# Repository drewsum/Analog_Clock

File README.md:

# Analog_Clock
An Analog Meter clock
Controlled by PIC32MZ EF

U1001 firmware is programmed onto U1001 with a PIC KIT 4 through header J801 (this is PIC32MZ EF firmware).

U1302 flash image is programmed onto U1302 through USB connector J1301 using FTProg (this is FTDI USB/UART bridge flash contents).

Analog panel meters are installed at MES1801, MES1901 and MES2001. Analog panel meters selected for this project were bought on ebay at: https://www.ebay.com/itm/DC-0-15V-Analog-Voltmeter-Analogue-Voltage-panel-meter-SO45-directly-Connect/183077594391?ssPageName=STRK%3AMEBIDX%3AIT&_trksid=p2057872.m2749.l2649

Custom meter face plates are printed from a PDF in the /misc folder, to scale. They are inserted into the panel meters to allow the clock to display the time.

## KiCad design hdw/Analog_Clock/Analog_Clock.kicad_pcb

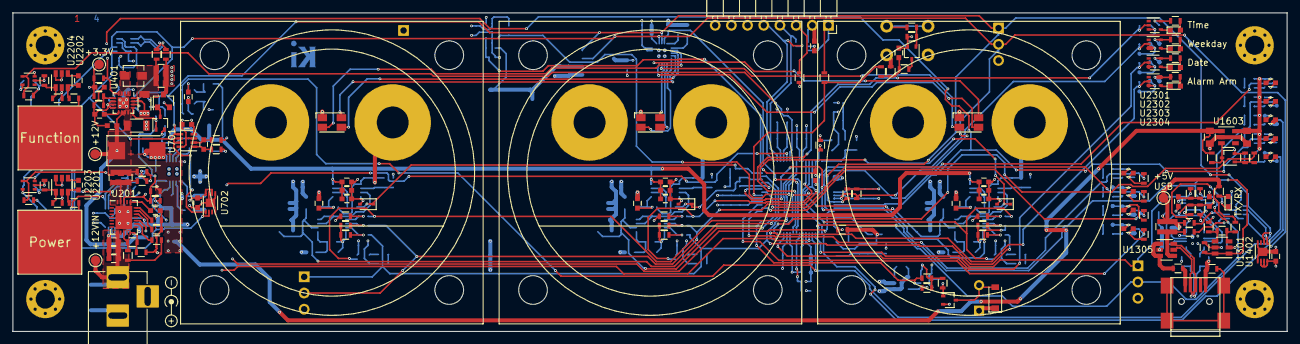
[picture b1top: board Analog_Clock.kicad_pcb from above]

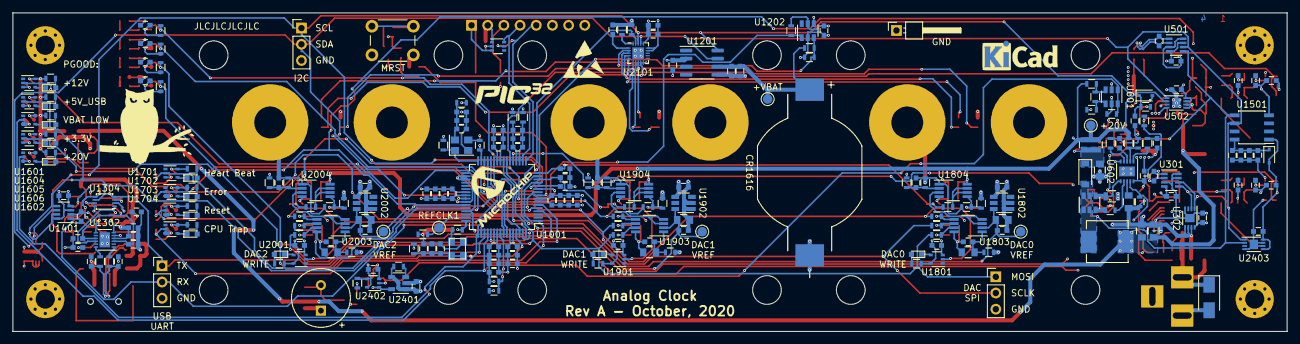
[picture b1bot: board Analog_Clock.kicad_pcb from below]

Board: 4 copper layers, 200.0 x 50.0 mm, 417 parts (203 on the bottom side), 202 nets.

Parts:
BT1202: CR1616_Holder; BAT_BU1632SM-JJ-GTR
BZ2401: CST-931RP-A; MagneticBuzzer_CUI_CST-931RP-A
C201, C203, C403, C904, C905, C910, C914, C918, C919, C1103, C1104, C1809, C1909, C2009, C2203, C2204: 10nF; C_0603
C202, C301, C302, C303, C404, C406, C501, C502, C503, C603, C604, C606, C701, C702, C703, C801, C802, C901, C902, C908, C912, C916, C917, C1101, C1102, C1202, C1203, C1204, C1205, C1301, C1302, C1304, C1306, C1307, C1310, C1312, C1401, C1402, C1403, C1504, C1602, C1603, C1605, C1606, C1607, C1701, C1702, C1703, C1704, C1801, C1802, C1806, C1807, C1808, C1811, C1812, C1901, C1902, C1906, C1907, C1908, C1911, C1912, C2001, C2002, C2006, C2007, C2008, C2011, C2012, C2103, C2201, C2202, C2207, C2208, C2301, C2302, C2303, C2304, C2401, C2402, C2403: 0.1uF; C_0603
C204, C906, C907, C911, C915, C920, C921, C1105, C1106, C1810, C1910, C2010: 1nF; C_0603
C205: 100uF; CP_Tantalum_Case-X_EIA-7343-43_Reflow
C401: 10uF; C_1206
C402, C903, C909, C913, C1201, C1303, C1501, C1502, C1503, C2101, C2102, C2205, C2206: 10uF; C_0603
C405: 100uF; C_1206
C601, C602, C607, C610: 10uF; C_0805
C605: 6.8nF; C_0603
C1309, C1311, C1805, C1905, C2005: 47pF; C_0603
C1601, C1604, C1803, C1804, C1903, C1904, C2003, C2004: 4.7uF; C_0805
D201: 24V; D_SMA
D401, D1501: BAT48JFILM; D_SOD-323
D601, D2401: MBR0580; D_SOD-123
D801: PESD3V3L5UY; SOT-363_SC-70-6
D1301, D2304: Yellow; LED_0603
D1601, D1602, D1603, D1605, D1701, D1801, D1901, D2001, D2301, D2302, D2303: Green; LED_0603
D1604, D1702, D1703, D1704: Red; LED_0603
D1802, D1902, D2002: ASMB-MTB0-0A3A2; LED_Avago_PLCC4_3.2x2.8mm_CW
D1803, D1903, D2003: BZX384-B3V3,115; D_SOD-323
H2501, H2502, H2503, H2504: 3mm Mounting Hole; MountingHole_3mm_Pad_Via
J201: +12V IN; BARREL_JACK
J801: PICKIT4; PICKIT4_Header
J1301: USB_B_Mini; USB_Mini-B
J2401: I2C; Pin_Header_Straight_1x03_Pitch2.54mm
J2402: USB UART; Pin_Header_Straight_1x03_Pitch2.54mm
J2403: DAC SPI; Pin_Header_Straight_1x03_Pitch2.54mm
L401: 3.3uH; L_Vishay_IHLP-1212
L601: 10uH; L_Vishay_IHLP-2525
L801, L802, L901, L902, L1101, L1102, L1301, L1302, L1801, L1901, L2001: 600R 0.5A; L_0603
MES1801, MES1901, MES2001: Voltmeter_DC; SO-45_Panel_Meter
Q401, Q801, Q1601, Q2401: BSS214NW; SOT-323_SC-70
Q402: ZXMS6004FFTA; SOT-23
Q601: FDC5612; SOT-23-6
R201: 51.1k; R_0603
R202: 1.15k; R_0603
R203, R209: 5.11k; R_0603
R204, R207, R211, R402, R403, R605, R607, R802, R804, R1001, R1002, R1102, R1103, R1106, R1107, R1203, R1305, R1602, R1603, R1701, R1702, R1705, R1706, R1804, R1805, R1807, R1904, R1905, R1907, R2004, R2005, R2007, R2101, R2203, R2204, R2205, R2206, R2207, R2208, R2301, R2302, R2305, R2306, R2402, R2403, R2405, R2407: 10k; R_0603
R205, R210, R401, R404, R406, R608, R610, R612, R801, R803, R1309, R1313, R1601, R1801, R1802, R1803, R1901, R1902, R1903, R2001, R2002, R2003, R2404, R2406: 10; R_0603
R206, R405, R1310: 0.02; R_0612
R208: 13k; R_0603
R407: 562k; R_0603
R408: 180k; R_0603
R601, R1306, R1308, R1314, R1315: 100k; R_0603
R602: 383; R_0603
R603: 1.87k; R_0603
R604, R613: 11.5k; R_0603
R606: 22k; R_0603
R609: 130m; R_0805
R611: 1; R_0612
R614, R805, R1301, R1604, R1605, R1606, R1607, R1608, R1703, R1704, R1707, R1708, R1806, R1812, R1906, R1912, R2006, R2012, R2303, R2304, R2307, R2308: 1k; R_0603
R1104, R1105: 100; R_0603
R1201, R2401: 1.07M; R_0603
R1202: 220k; R_0603
R1302: 487k; R_0603
R1303: 6.04k; R_0603
R1304: 40.2k; R_0603
R1311, R1312: 27; R_0603
R1808, R1809, R1908, R1909, R2008, R2009: 1.01k; R_0603
R1810, R1811, R1910, R1911, R2010, R2011: 9.09k; R_0603
R2102: 3.65k; R_0603
R2201, R2202: 499; R_0603
SW801: MRST; SW_PUSH_6mm
SW2201, SW2202: Cap_Touch; Capacitive_Touch_Pad
TP201: TP; Pin_Header_Angled_1x01_Pitch2.54mm
TP202, TP203, TP1801, TP1901, TP2001: TP_Pad; Test_Point
TP401, TP601, TP1102, TP1201, TP1301: TP; Test_Point
U201: TPS26600RHFT; QFN-24-1EP_4x5mm_Pitch0.5mm
U301, U501, U701, U1401: INA219BxDCN; SOT-23-8
U302, U502, U702, U1402, U2403: MCP9804; DFN-8-1EP_3x2mm_P0.5mm_EP1.3x1.5mm
U401: TPS62150; QFN-16-1EP_3x3mm_P0.5mm_EP1.8x1.8mm
U601, U1202, U1301: TLV6700; SOT-23-6
U602: LT3757; DFN-10-1EP_3x3mm_Pitch0.5mm
U1001: PIC32MZ0512EFE064T-I_PT; TQFP-64_10x10mm_P0.5mm
U1201: DS3231MZ; SOIC-8_3.9x4.9mm_P1.27mm
U1302: FT234XD; DFN-12-1EP_3x3mm_Pitch0.45mm
U1304: TXB0102DCU; VSSOP-8_2.4x2.1mm_P0.5mm
U1305: TPD3S014DBVR; SOT-23-6
U1501: DS1683; SOIC-8_3.9x4.9mm_Pitch1.27mm
U1601, U1602, U1604, U1606, U1701, U1702, U1703, U1704, U2301, U2302, U2303, U2304: 74LVC1G06; SOT-353_SC-70-5
U1603: LP2985-3.3; SOT-23-5
U1605, U1801, U1901, U2001: 74LVC1G07; SOT-353_SC-70-5
U1802, U1902, U2002: LT1790-2.048; TSOT-23-6
U1803, U1903, U2003: DAC8551; VSSOP-8_3.0x3.0mm_P0.65mm
U1804, U1904, U2004: OPA2197xDGK; VSSOP-8_3.0x3.0mm_P0.65mm
U2101: LP5009; UQFN-20-1EP_3x3mm_Pitch0.4mm
U2201, U2202: AT42QT1010-TSHR; SOT-23-6
U2203, U2204: 74LVC1G17; SOT-353_SC-70-5
U2401: LTC6900; SOT-23-5
U2402: 74LVC1G08; SOT-353_SC-70-5
X1101: ASE-8.000MHz; Oscillator_SMD_Abracon_ASE-4Pin_3.2x2.5mm
X1102: ECS-327KE

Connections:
+3.3VA_MZ: C917.1, C919.1, C921.1, L901.1, U1001.19
+3.3V_PGL: C1602.1, C1604.1, R1604.1, R1605.1, R1606.1, R1607.1, R1608.1, U1601.5, U1603.5
+3.3V_USB: C1301.1, C1307.1, C1312.1, R1314.1, R1315.1, U1302.3, U1302.9, U1304.7
+3V3: BZ2401.1, C302.1, C303.1, C406.1, C502.1, C503.1, C606.1, C702.1, C703.1, C802.1, C901.1, C902.1, C903.1, C904.1, C905.1, C906.1, C907.1, C908.1, C909.1, C910.1, C911.1, C912.1, C913.1, C914.1, C915.1, C916.1, C918.1, C920.1, C1203.1, C1204.1, C1304.1, C1310.1, C1402.1, C1403.1, C1603.1, C1605.1, C1606.1, C1607.1, C1701.1, C1702.1, C1703.1, C1704.1, C1801.1, C1802.1, C1901.1, C1902.1, C2001.1, C2002.1, C2102.1, C2103.1, C2201.1, C2202.1, C2207.1, C2208.1, C2301.1, C2302.1, C2303.1, C2304.1, C2401.1, C2402.1, C2403.1, D401.2, D801.1, D1501.2, D1802.1, D1902.1, D2002.1, D2401.1, J801.2, L901.2, L1101.2, L1102.2, L1801.2, L1901.2, L2001.2, Q402.3, R402.1, R405.2, R406.2, R407.1, R607.2, R804.1, R1001.1, R1002.1, R1203.1, R1305.1, R1306.1, R1308.1, R1703.1, R1704.1, R1705.1, R1707.1, R1708.1, R1804.1, R1806.1, R1904.1, R1906.1, R2004.1, R2006.1, R2303.1, R2304.1, R2307.1, R2308.1, R2401.1, R2403.1, SW801.1, TP401.1, U301.4, U302.8, U401.14, U501.4, U501.7, U502.7, U502.8, U601.5, U701.4, U702.6, U702.8, U1001.8, U1001.26, U1001.39, U1001.54, U1001.60, U1201.2, U1202.5, U1301.5, U1304.3, U1401.4, U1402.6, U1402.7, U1402.8, U1501.1, U1602.5, U1604.5, U1605.5, U1606.5, U1701.5, U1702.5, U1703.5, U1704.5, U1801.5, U1802.4, U1901.5, U1902.4, U2001.5, U2002.4, U2101.16, U2201.5, U2201.6, U2202.5, U2202.6, U2203.5, U2204.5, U2301.5, U2302.5, U2303.5, U2304.5, U2401.1, U2401.4, U2402.5, U2403.5, U2403.8
+5V_USB: C1302.1, C1303.1, C1306.1, R1301.1, R1302.1, R1309.2, R1310.1, TP1301.1, U1302.4
+12V: C205.1, C401.1, C404.1, C601.1, C602.1, C604.1, C1601.1, L601.1, R206.2, R208.1, R210.2, R1603.1, TP203.1, U401.10, U401.11, U401.12, U602.10, U1603.1
+12Vin: C202.1, C203.1, C204.1, D201.1, J201.1, R201.1, R204.1, TP202.1, U201.8, U201.9
+20V: C1808.1, C1809.1, C1810.1, C1908.1, C1909.1, C1910.1, C2008.1, C2009.1, C2010.1, R601.1, R611.2, R612.1, R613.1, TP601.1, U1804.8, U1904.8, U2004.8
/USB UART Bridge/BRIDGE_USB+: R1311.2, U1302.12
/USB UART Bridge/BRIDGE_USB-: R1312.2, U1302.1
/USB UART Bridge/CONN_USB+: C1309.1, J1301.3, R1311.1, U1305.6
/USB UART Bridge/CONN_USB-: C1311.1, J1301.2, R1312.1, U1305.5
Alarm_Arm_LED: R2306.1, U1001.63, U2304.2
Buzzer_Enable: R2405.2, U1001.1, U2402.2
CPU_Trap_LED: R1706.1, U1001.6, U1704.2
Cap_Touch_Function: R2208.1, U1001.22, U2204.4
Cap_Touch_Power: R2207.1, U1001.21, U2203.4
DAC0_VREF: C1803.1, C1805.1, TP1801.1, U1001.15, U1802.6, U1803.2
DAC1_VREF: C1903.1, C1905.1, TP1901.1, U1001.13, U1902.6, U1903.2
DAC2_VREF: C2003.1, C2005.1, TP2001.1, U1001.11, U2002.6, U2003.2
DAC_SPI_MOSI: J2403.1, R1802.1, R1902.1, R2002.1, U1001.23
DAC_SPI_SCLK: J2403.2, R1803.1, R1903.1, R2003.1, U1001.29
Error_LED: R1702.1, U1001.10, U1702.2
Function_Date_LED: R2305.1, U1001.61, U2303.2
Function_Time_LED: R2301.1, U1001.58, U2301.2
Function_Weekday_LED: R2302.1, U1001.62, U2302.2
GND: BT1202.2, C202.2, C203.2, C204.2, C205.2, C302.2, C303.2, C401.2, C402.2, C403.2, C404.2, C405.2, C406.2, C502.2, C503.2, C601.2, C602.2, C603.2, C604.2, C605.2, C606.2, C607.2, C610.2, C702.2, C703.2, C801.2, C802.2, C901.2, C902.2, C903.2, C904.2, C905.2, C906.2, C907.2, C908.2, C909.2, C910.2, C911.2, C912.2, C913.2, C914.2, C915.2, C916.2, C918.2, C920.2, C1101.2, C1102.2, C1103.2, C1104.2, C1105.2, C1106.2, C1201.2, C1202.2, C1203.2, C1204.2, C1205.2, C1301.2, C1302.2, C1303.2, C1304.2, C1306.2, C1307.2, C1309.2, C1310.2, C1311.2, C1312.2, C1402.2, C1403.2, C1501.2, C1502.2, C1503.2, C1504.2, C1601.2, C1602.2, C1603.2, C1604.2, C1605.2, C1606.2, C1607.2, C1701.2, C1702.2, C1703.2, C1704.2, C1801.2, C1802.2, C1803.2, C1804.2, C1805.2, C1806.2, C1807.2, C1808.2, C1809.2, C1810.2, C1812.2, C1901.2, C1902.2, C1903.2, C1904.2, C1905.2, C1906.2, C1907.2, C1908.2, C1909.2, C1910.2, C1912.2, C2001.2, C2002.2, C2003.2, C2004.2, C2005.2, C2006.2, C2007.2, C2008.2, C2009.2, C2010.2, C2012.2, C2101.2, C2102.2, C2103.2, C2201.2, C2202.2, C2205.2, C2206.2, C2207.2, C2208.2, C2301.2, C2302.2, C2303.2, C2304.2, C2401.2, C2402.2, C2403.2, D201.2, D801.2, D1803.2, D1903.2, D2003.2, J201.2, J201.3, J1301.5, J2401.3, J2402.3, J2403.3, L802.2, L902.2, L1302.1, MES1801.1, MES1901.1, MES2001.1, Q401.2, Q402.2, Q801.2, Q1601.2, Q2401.2, R209.2, R408.2, R603.2, R604.2, R605.2, R609.2, R614.2, R802.2, R1102.2, R1103.2, R1106.2, R1107.2, R1202.2, R1304.2, R1602.2, R1701.2, R1702.2, R1706.2, R1805.2, R1807.2, R1808.2, R1809.2, R1905.2, R1907.2, R1908.2, R1909.2, R2005.2, R2007.2, R2008.2, R2009.2, R2101.2, R2102.2, R2203.2, R2204.2, R2207.2, R2208.2, R2301.2, R2302.2, R2305.2, R2306.2, R2402.1, R2404.2, R2405.1, R2407.1, TP201.1, U201.17, U301.3, U301.7, U301.8, U302.4, U302.5, U302.6, U302.7, U302.9, U401.6, U401.7, U401.8, U401.15, U401.16, U401.17, U501.3, U501.8, U502.4, U502.5, U502.6, U502.9, U601.2, U602.5, U602.11, U701.3, U701.8, U702.4, U702.5, U702.7, U702.9, U1001.7, U1001.25, U1001.34, U1001.35, U1001.40, U1001.55, U1001.59, U1201.5, U1202.2, U1202.4, U1301.2, U1302.5, U1302.13, U1304.2, U1305.2, U1401.3, U1401.8, U1402.4, U1402.5, U1402.9, U1501.4, U1601.3, U1602.3, U1603.2, U1604.3, U1605.3, U1606.3, U1701.3, U1702.3, U1703.3, U1704.3, U1801.3, U1802.1, U1802.2, U1803.8, U1804.4, U1901.3, U1902.1, U1902.2, U1903.8, U1904.4, U2001.3, U2002.1, U2002.2, U2003.8, U2004.4, U2101.14, U2101.15, U2101.21, U2201.2, U2202.2, U2203.3, U2204.3, U2301.3, U2302.3, U2303.3, U2304.3, U2401.2, U2402.3, U2403.4, U2403.6, U2403.7, U2403.9, X1101.2, X1102.2
GNDA_MZ: C917.2, C919.2, C921.2, L902.1, U1001.20
Heartbeat_LED: R1701.1, U1001.4, U1701.2
I2C_SCL: J2401.1, R1002.2, U301.5, U302.2, U501.5, U502.2, U701.5, U702.2, U1001.42, U1201.8, U1401.5, U1401.7, U1402.2, U1501.5, U2101.18, U2403.2
I2C_SDA: J2401.2, R1001.2, U301.6, U302.1, U501.6, U502.1, U701.6, U701.7, U702.1, U1001.41, U1201.7, U1401.6, U1402.1, U1501.6, U2101.17, U2403.1
METER0_LED_B: D1802.2, U2101.4
METER0_LED_G: D1802.3, U2101.3
METER0_LED_R: D1802.4, U2101.2
METER1_LED_B: D1902.2, U2101.7
METER1_LED_G: D1902.3, U2101.6
METER1_LED_R: D1902.4, U2101.5
METER2_LED_B: D2002.2, U2101.10
METER2_LED_G: D2002.3, U2101.9
METER2_LED_R: D2002.4, U2101.8
Meter_LED_Enable: R2101.1, U1001.57, U2101.19
unnamed: BZ2401.2, D2401.2, Q2401.3
unnamed: C201.1, U201.20
unnamed: C201.2, R203.2, R207.2, R211.2, U201.15, U201.25
unnamed: C402.1, D401.1, R403.1
unnamed: C403.1, U401.9
unnamed: C405.1, L401.2, R404.2, R405.1
unnamed: C603.1, U602.3
unnamed: C605.1, R606.2
unnamed: C607.1, U602.8
unnamed: C610.1, D601.1, R610.1, R611.1
unnamed: C801.1, R803.2, R804.2, R805.2
unnamed: C1101.1, C1103.1, C1105.1, L1101.1, X1101.4
unnamed: C1102.1, C1104.1, C1106.1, L1102.1, X1102.1, X1102.4
unnamed: C1501.1, C1502.1, C1503.1, C1504.1, D1501.1, U1501.8
unnamed: C1804.1, C1806.1, L1801.1, U1803.1
unnamed: C1807.1, R1808.1, R1810.2, U1804.5
unnamed: C1811.1, MES1801.2, R1810.1, R1811.1, U1804.1
unnamed: C1811.2, R1809.1, R1811.2, U1804.2
unnamed: C1904.1, C1906.1, L1901.1, U1903.1
unnamed: C1907.1, R1908.1, R1910.2, U1904.5
unnamed: C1911.1, MES1901.2, R1910.1, R1911.1, U1904.1
unnamed: C1911.2, R1909.1, R1911.2, U1904.2
unnamed: C2004.1, C2006.1, L2001.1, U2003.1
unnamed: C2007.1, R2008.1, R2010.2, U2004.5
unnamed: C2011.1, MES2001.2, R2010.1, R2011.1, U2004.1
unnamed: C2011.2, R2009.1, R2011.2, U2004.2
unnamed: C2101.1, U2101.1
unnamed: C2203.1, U2201.4
unnamed: C2203.2, R2201.2, U2201.3
unnamed: C2204.1, U2202.4
unnamed: C2204.2, R2202.2, U2202.3
unnamed: C2205.1, R2205.1, U2203.2
unnamed: C2206.1, R2206.1, U2204.2
unnamed: D601.2, L601.2, Q601.1, Q601.2, Q601.5, Q601.6
unnamed: D801.3, J801.1, L801.2
unnamed: D1301.2, R1301.2
unnamed: D1601.1, U1601.4
unnamed: D1601.2, R1604.2
unnamed: D1602.1, U1602.4
unnamed: D1602.2, R1605.2
unnamed: D1603.1, U1604.4
unnamed: D1603.2, R1606.2
unnamed: D1604.1, U1605.4
unnamed: D1604.2, R1607.2
unnamed: D1605.1, U1606.4
unnamed: D1605.2, R1608.2
unnamed: D1701.1, U1701.4
unnamed: D1701.2, R1703.2
unnamed: D1702.1, U1702.4
unnamed: D1702.2, R1704.2
unnamed: D1703.1, U1703.4
unnamed: D1703.2, R1707.2
unnamed: D1704.1, U1704.4
unnamed: D1704.2, R1708.2
unnamed: D1801.1, U1801.4
unnamed: D1801.2, R1806.2
unnamed: D1901.1, U1901.4
unnamed: D1901.2, R1906.2
unnamed: D2001.1, U2001.4
unnamed: D2001.2, R2006.2
unnamed: D2301.1, U2301.4
unnamed: D2301.2, R2303.2
unnamed: D2302.1, U2302.4
unnamed: D2302.2, R2304.2
unnamed: D2303.1, U2303.4
unnamed: D2303.2, R2307.2
unnamed: D2304.1, U2304.4
unnamed: D2304.2, R2308.2
unnamed: J801.3, L802.1
unnamed: J1301.1, L1301.1
unnamed: J1301.6, L1302.2
unnamed: L401.1, U401.1, U401.2, U401.3
unnamed: L1301.2, U1305.1, U1305.3
unnamed: Q401.3, Q402.1, R403.2
unnamed: Q601.3, R608.1
unnamed: Q601.4, R609.1, U602.6
unnamed: Q801.1, R801.2, R802.1
unnamed: Q801.3, R803.1
unnamed: Q1601.1, R1601.2, R1602.1
unnamed: Q1601.3, R1603.2, U1603.3
unnamed: Q2401.1, R2406.1, R2407.2
unnamed: R201.2, R202.1, U201.10
unnamed: R202.2, R203.1, U201.12
unnamed: R204.2, U201.14
unnamed: R205.2, R206.1, U201.23, U201.24
unnamed: R207.1, U201.19
unnamed: R211.1, U201.18
unnamed: R407.2, R408.1, U401.5
unnamed: R601.2, R602.1, U601.3
unnamed: R602.2, R603.1, U601.4
unnamed: R604.1, U602.4
unnamed: R606.1, U602.1
unnamed: R608.2, U602.7
unnamed: R613.2, R614.1, U602.2
unnamed: R801.1, SW801.2
unnamed: R1104.1, X1101.3
unnamed: R1105.1, X1102.3
unnamed: R1302.2, R1303.1, U1301.3
unnamed: R1303.2, R1304.1, U1301.4
unnamed: R1310.2, R1313.2, U1305.4
unnamed: R1801.2, R1804.2, U1803.5
unnamed: R1802.2, R1805.1, U1803.7
unnamed: R1803.2, R1807.1, U1803.6
unnamed: R1812.2, U1804.6, U1804.7
unnamed: R1901.2, R1904.2, U1903.5
unnamed: R1902.2, R1905.1, U1903.7
unnamed: R1903.2, R1907.1, U1903.6
unnamed: R1912.2, U1904.6, U1904.7
unnamed: R2001.2, R2004.2, U2003.5
unnamed: R2002.2, R2005.1, U2003.7
unnamed: R2003.2, R2007.1, U2003.6
unnamed: R2012.2, U2004.6, U2004.7
unnamed: R2102.1, U2101.20
unnamed: R2201.1, SW2201.1
unnamed: R2202.1, SW2202.1
unnamed: R2203.1, R2205.2, U2201.1
unnamed: R2204.1, R2206.2, U2202.1
unnamed: R2401.2, U2401.3
unnamed: R2402.2, U2401.5, U2402.1
unnamed: R2406.2, U2402.4
unnamed: U1803.3, U1803.4, U1804.3
unnamed: U1903.3, U1903.4, U1904.3
unnamed: U2003.3, U2003.4, U2004.3
PIC32MZ_ICSPCLK: D801.5, J801.5, U1001.17
PIC32MZ_ICSPDAT: D801.6, J801.4, U1001.18
PIC32MZ_POSC_EC: R1104.2, R1106.1, U1001.31
PIC32MZ_POSC_EC_Enable: R1103.1, U1001.32, X1101.1
PIC32MZ_REFCLK1: R1102.1, TP1102.1, U1001.47
PIC32MZ_SOSC: R1105.2, R1107.1, U1001.48
POS3P3_PGL_SHDN: R1601.1, U1001.64
POS3P3_PGOOD: R402.2, U401.4, U1001.43, U1606.2
POS3P3_RUN: Q401.1, R401.1, U401.13
POS3P3_SNS+: C501.1, R404.1, U501.1
POS3P3_SNS-: C501.2, R406.1, U501.2
POS5_USB_PGOOD: R1305.2, U1001.44, U1301.1, U1301.6, U1304.6, U1604.2
POS5_USB_SNS+: C1401.1, R1313.1, U1401.1
POS5_USB_SNS-: C1401.2, R1309.1, U1401.2
POS12_PGOOD: R208.2, R209.1, R401.2, U201.22, U1001.45, U1601.2
POS12_SNS+: C301.1, R205.1, U301.1
POS12_SNS-: C301.2, R210.1, U301.2
POS20_PGOOD: R607.1, U601.1, U601.6, U1001.52, U1602.2
POS20_RUN: R605.1, U602.9, U1001.53
POS20_SNS+: C701.1, R610.2, U701.1
POS20_SNS-: C701.2, R612.2, U701.2
Reset_LED: R1705.2, U1001.5, U1703.2
Telemetry_Hardstrap: R2403.2, R2404.1, U1001.56
USB_UART_RX: J2402.2, R1308.2, U1001.50, U1304.5
USB_UART_RX_BUF: R1314.2, U1302.7, U1304.8
USB_UART_TX: J2402.1, R1306.2, U1001.51, U1304.4
USB_UART_TX_BUF: R1315.2, U1302.10, U1304.1
VBAT: BT1202.1, C1201.1, C1202.1, R1201.1, TP1201.1, U1201.6
VBAT_ADC: C1205.1, R1201.2, R1202.1, U1001.30, U1202.3
VBAT_PGOOD: R1203.2, U1001.49, U1202.1, U1605.2
VDAC_0_ADC: C1812.1, D1803.1, R1812.1, U1001.16
VDAC_1_ADC: C1912.1, D1903.1, R1912.1, U1001.14
VDAC_2_ADC: C2012.1, D2003.1, R2012.1, U1001.12
~DAC_SPI_SYNC_0: R1801.1, U1001.24, U1801.2
~DAC_SPI_SYNC_1: R1901.1, U1001.27, U1901.2
~DAC_SPI_SYNC_2: R2001.1, U1001.28, U2001.2
~PIC32MZ_MCLR: L801.1, R805.1, U1001.9
~USB_ACTIVE: D1301.1, U1302.6

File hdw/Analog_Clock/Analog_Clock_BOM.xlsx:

Qty | Reference(s) | Value | Digi-Key PN
1 | BT1201 | CR1616 | P034-ND
1 | BT1202 | CR1616_Holder | BU1632SM-JJ-GCT-ND
1 | BZ2401 | CST-931RP-A | 102-1461-ND
16 | C201, C203, C403, C904, C905, C910, C914, C918, C919, C1103, C1104, C1809, C190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 | 10nF | 399-7842-1-ND
82 | C202, C301, C302, C303, C404, C406, C501, C502, C503, C603, C604, C606, C701, C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 | 0.1uF | 399-7845-1-ND
12 | C204, C906, C907, C911, C915, C920, C921, C1105, C1106, C1810, C1910, C2010 | 1nF | 399-1083-1-ND
1 | C205 | 100uF | 718-1102-1-ND
1 | C401 | 10uF | 1276-7031-1-ND
13 | C402, C903, C909, C913, C1201, C1303, C1501, C1502, C1503, C2101, C2102, C2205,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 | 10uF | 490-10474-1-ND
1 | C405 | 100uF | 587-1963-1-ND
4 | C601, C602, C607, C610 | 10uF | 490-18664-1-ND
1 | C605 | 6.8nF | 399-1089-1-ND
5 | C1309, C1311, C1805, C1905, C2005 | 47pF | 399-7918-1-ND
8 | C1601, C1604, C1803, C1804, C1903, C1904, C2003, C2004 | 4.7uF | 1276-2970-1-ND
1 | D201 | 24V | SMAJ24CALFCT-ND
2 | D401, D1501 | BAT48JFILM | 497-5711-1-ND
2 | D601, D2401 | MBR0580 | MBR0580S1-7DICT-ND
1 | D801 | PESD3V3L5UY | 1727-3828-1-ND
2 | D1301, D2304 | Yellow | 754-1124-1-ND
11 | D1601, D1602, D1603, D1605, D1701, D1801, D1901, D2001, D2301, D2302, D2303 | Green | 754-1121-1-ND
4 | D1604, D1702, D1703, D1704 | Red | 754-1117-1-ND
3 | D1802, D1902, D2002 | ASMB-MTB0-0A3A2 | 516-3279-1-ND
3 | D1803, D1903, D2003 | BZX384-B3V3,115 | 1727-3654-1-ND
1 | J1301 | USB_B_Mini | 732-2109-1-ND
1 | L401 | 3.3uH | 541-2567-1-ND
1 | L601 | 10uH | 541-1013-1-ND
11 | L801, L802, L901, L902, L1101, L1102, L1301, L1302, L1801, L1901, L2001 | 600R 0.5A | 732-1593-1-ND
28 | MK1801, MK1802, MK1805, MK1806, MK1807, MK1808, MK1811, MK1812, MK1901, MK1902,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 | #4-40 Screw | 36-9900-ND
16 | MK1803, MK1804, MK1809, MK1810, MK1903, MK1904, MK1909, MK1910, MK2003, MK2004,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 | #4-40 Standoff | 1772-1052-ND
1 | N201 | +12V 1A Power Supply | 993-1335-ND
3 | Q401, Q801, Q1601 | BSS214NW | BSS214NWH6327XTSA1CT-ND
1 | Q402 | ZXMS6004FFTA | ZXMS6004FFCT-ND
1 | Q601 | FDC5612 | FDC5612CT-ND
1 | Q2401 | BSS214NW | BSS214NWH6327XTSA1CT-ND
1 | R201 | 51.1k | RMCF0603FT51K1TR-ND
1 | R202 | 1.15k | RMCF0603FT1K15CT-ND
2 | R203, R209 | 5.11k | CR0603-FX-5111ELFCT-ND
47 | R204, R207, R211, R402, R403, R605, R607, R802, R804, R1001, R1002, R1102, R110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 | 10k | YAG2321CT-ND
24 | R205, R210, R401, R404, R406, R608, R610, R612, R801, R803, R1309, R1313, R1601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 | 10 | YAG2321CT-ND
3 | R206, R405, R1310 | 0.02 | P16010CT-ND
1 | R208 | 13k | 311-13.0KHRCT-ND
1 | R407 | 562k | 311-562KHRCT-ND
1 | R408 | 180k | 311-180KHRCT-ND
5 | R601, R1306, R1308, R1314, R1315 | 100k | RMCF0603FT100KCT-ND
1 | R602 | 383 | 311-383HRCT-ND
1 | R603 | 1.87k | 311-1.87KHRCT-ND
2 | R604, R613 | 11.5k | 311-11.5KHRCT-ND
1 | R606 | 22k | 311-22KLDCT-ND
1 | R609 | 130m | RL12S.13FCT-ND
1 | R611 | 1 | RHM1220CT-ND
22 | R614, R805, R1301, R1604, R1605, R1606, R1607, R1608, R1703, R1704, R1707, R170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 | 1k | 311-1.00KHRCT-ND
2 | R1104, R1105 | 100 | RMCF0603FT100RCT-ND
2 | R1201, R2401 | 1.07M | RMCF0603FT1M07CT-ND
1 | R1202 | 220k | RMCF0603FT220KCT-ND
1 | R1302 | 487k | 311-487KHRCT-ND
1 | R1303 | 6.04k | RMCF0603FT6K04CT-ND
1 | R1304 | 40.2k | RMCF0603FT40K2CT-ND
2 | R1311, R1312 | 27 | 311-27.0HRCT-ND
6 | R1808, R1809, R1908, R1909, R2008, R2009 | 1.01k | YAG4489CT-ND
6 | R1810, R1811, R1910, R1911, R2010, R2011 | 9.09k | YAG1755CT-ND
1 | R2102 | 3.65k | YAG4547CT-ND
2 | R2201, R2202 | 499 | RMCF0603FT499RCT-ND
1 | U201 | TPS26600RHFT | 296-45478-1-ND
4 | U301, U501, U701, U1401 | INA219BxDCN | 296-46420-1-ND
5 | U302, U502, U702, U1402, U2403 | MCP9804 | MCP9804T-E/MCCT-ND
1 | U401 | TPS62150 | 296-41757-1-ND
2 | U601, U1301 | TLV6700 | 296-51696-1-ND
1 | U602 | LT3757 | LT3757EDD#PBF-ND
1 | U1001 | PIC32MZ0512EFE064T-I_PT | PIC32MZ0512EFE064T-I/PTCT-ND
1 | U1201 | DS3231MZ | DS3231MZ+-ND
1 | U1202 | TLV6700 | 296-51696-1-ND
1 | U1302 | FT234XD | 768-1178-1-ND
1 | U1304 | TXB0102DCU | 296-22862-1-ND
1 | U1305 | TPD3S014DBVR | 296-38835-1-ND
1 | U1501 | DS1683 | DS1683S+-ND
12 | U1601, U1602, U1604, U1606, U1701, U1702, U1703, U1704, U2301, U2302, U2303, U2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 | 74LVC1G06 | 296-8484-1-ND
1 | U1603 | LP2985-3.3 | LP2985IM5X-3.3/NOPBCT-ND
4 | U1605, U1801, U1901, U2001 | 74LVC1G07 | 296-8486-1-ND
3 | U1802, U1902, U2002 | LT1790-2.048 | LT1790BIS6-2.048#TRMPBFCT-ND
3 | U1803, U1903, U2003 | DAC8551 | 296-38925-1-ND
3 | U1804, U1904, U2004 | OPA2197xDGK | 296-44774-1-ND
1 | U2101 | LP5009 | 296-LP5009RUKRCT-ND
2 | U2201, U2202 | AT42QT1010-TSHR | AT42QT1010-TSHRCT-ND
2 | U2203, U2204 | 74LVC1G17 | 296-11934-1-ND
1 | U2401 | LTC6900 | LTC6900CS5#TRMPBFCT-ND
1 | U2402 | 74LVC1G08 | 296-11602-1-ND
1 | X1101 | ASE-8.000MHz | 535-9558-1-ND
1 | X1102 | ECS-327KE | XC1751CT-ND

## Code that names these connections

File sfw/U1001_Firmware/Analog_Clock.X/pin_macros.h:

#ifndef _PIN_MACROS_H    /* Guard against multiple inclusion */
#define _PIN_MACROS_H


#include <xc.h>

#define HIGH    1
#define LOW     0

// These pin macros allow for easier manipulation of GPIO with matching
// signal names from the hardware schematic

// Port A
// NO PORT A

// Port B
#define CAP_TOUCH_POWER_PIN         PORTBbits.RB8
#define CAP_TOUCH_FUNCTION_PIN      PORTBbits.RB9
#define nDAC_SPI_SYNC_0_PIN         LATBbits.LATB11
#define nDAC_SPI_SYNC_1_PIN         LATBbits.LATB12
#define nDAC_SPI_SYNC_2_PIN         LATBbits.LATB13

// Port C
#define POSC_EC_ENABLE_PIN          LATCbits.LATC15

// Port D
#define VBAT_PGOOD_PIN              PORTDbits.RD1
#define POS20_PGOOD_PIN             PORTDbits.RD4
#define POS20_RUN_PIN               LATDbits.LATD5
#define POS3P3_PGOOD_PIN            PORTDbits.RD9
#define POS5_USB_PGOOD_PIN          PORTDbits.RD10
#define POS12_PGOOD_PIN             PORTDbits.RD11

// Port E
#define FUNCTION_TIME_LED_PIN       LATEbits.LATE0
#define FUNCTION_DATE_LED_PIN       LATEbits.LATE1
#define FUNCTION_WEEKDAY_LED_PIN    LATEbits.LATE2
#define ALARM_ARM_LED_PIN           LATEbits.LATE3
#define POS3P3_PGL_SHDN_PIN         LATEbits.LATE4
#define BUZZER_ENABLE_PIN           LATEbits.LATE5

// Port F
#define TELEMETRY_HARDSTRAP_PIN     PORTFbits.RF0
#define METER_LED_ENABLE_PIN        LATFbits.LATF1

// Port G
#define HEARTBEAT_LED_PIN           LATGbits.LATG6
#define RESET_LED_PIN               LATGbits.LATG7
#define CPU_TRAP_LED_PIN            LATGbits.LATG8
#define ERROR_LED_PIN               LATGbits.LATG9

#endif /* _PIN_MACROS_H */

/* *****************************************************************************
 End of File
 */

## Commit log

2020-04-13 Started KiCad project
2020-04-17 More schematic work
2020-08-01 a few sch adjustments
2020-08-03 More sch work
2020-08-04 more sch progress
2020-08-06 Added +20V power supply, updated input power sheet
2020-08-08 some +20V boost supply work
2020-08-13 more analog work, added some more sch stuff
2020-08-15 big sch push
2020-08-15 Much more schematic progress
2020-08-15 made netlist, started PCB
2020-08-16 Changed VBAT ADC circuit
2020-08-16 started arranging parts on PCB
2020-08-20 more PCB grouping
2020-08-25 Arranged more components on PCB
2020-09-20 More PCB arrangement
2020-09-20 Major USB restructuring
2020-09-20 Finished arranging parts, few netlist changes
2020-09-20 Board outline
2020-09-20 more PCB placement
2020-09-20 moar PCB placement
2020-09-20 finished first pass PCB placement
2020-09-21 A lot more PCB work
2020-09-26 started routing
2020-09-26 more routing
2020-09-27 moar routing
2020-09-27 finished routing subcircuits
2020-09-27 autorouting, cleanups
2020-10-15 Added BOM
2020-10-15 Created MPLABX Firmware Project
2020-10-15 got PIC booting out of reset, setting up GPIO, clocking
2020-10-19 Fixed some GPIO/OSC setup issues
2020-10-19 ported heartbeat timer
2020-10-20 added some clock stability changes at boot
2020-10-20 got heartbeat PWM working, ported error handler and WDT
2020-10-20 ported heartbeat services, more stability attempts
2020-10-20 ported USB UART, associated code
2020-10-20 few USB command fixes
2020-10-20 strong fixes
2020-10-21 ported prefetch
2020-10-21 ported PMD, PGOOD monitor stuff
2020-10-21 consolidating a lot of commands into platform status
2020-10-21 ported cause of reset
2020-10-21 ported I2C master code
2020-10-22 Ported temp sensors
2020-10-22 ported power monitors
2020-10-22 ported live telemetry
2020-10-22 ported RTCC code
2020-10-22 creating new set RTCC command to replace four older ones
2020-10-24 combined all RTCC set commands into one serial command
2020-10-25 Ported backup RTC code, untested
2020-10-26 finished porting backup rtc stuff
2020-10-28 added FTDI image
2020-10-28 got basic ADC stuff working
2020-10-30 solved some ADC issues
2020-10-30 got last ADC channel working
2020-10-30 started LP5009 led driver code
2020-10-30 added LP5009 print status function
2020-10-30 added LP5009 startup delay
2020-10-31 Added a lot of backlight serial commands
2020-10-31 Added basic cap button code
2020-11-01 added -h flag to serial commands
2020-11-02 Added SPI DAC control code, SPI master port code
2020-11-02 Some bug fixes, some SPI DAC progress
2020-11-03 Got SPI DACs working
2020-11-03 Added lots of user interface
2020-11-04 added lots of code to control meters based on time, date, etc
2020-11-04 added PGOOD disable on power button press
2020-11-05 started on meter inserts
2020-11-05 more meter insert work
2020-11-07 finished face plate files
2020-11-09 few software improvements
2020-11-09 some more shutdown code
2020-11-12 fine tuned meter dial position for time, date and weekday
2020-11-13 Added code for controlling clock pushbuttons over serial
2020-11-13 Ported alarm code
2020-11-13 got IDLE mode working
2020-11-13 bug fixes, added DAC power down
2020-11-13 MCU firmware version 1.0
2020-11-13 added image of completed project
2020-12-06 meter range recalibration, INA219 status bug fixes
2020-12-06 added inverted meter inserts
2022-01-07 Update pgood_monitor.c
    fixed bug with `POS3P3_PGL_SHDN_PIN` reference in power good monitor
